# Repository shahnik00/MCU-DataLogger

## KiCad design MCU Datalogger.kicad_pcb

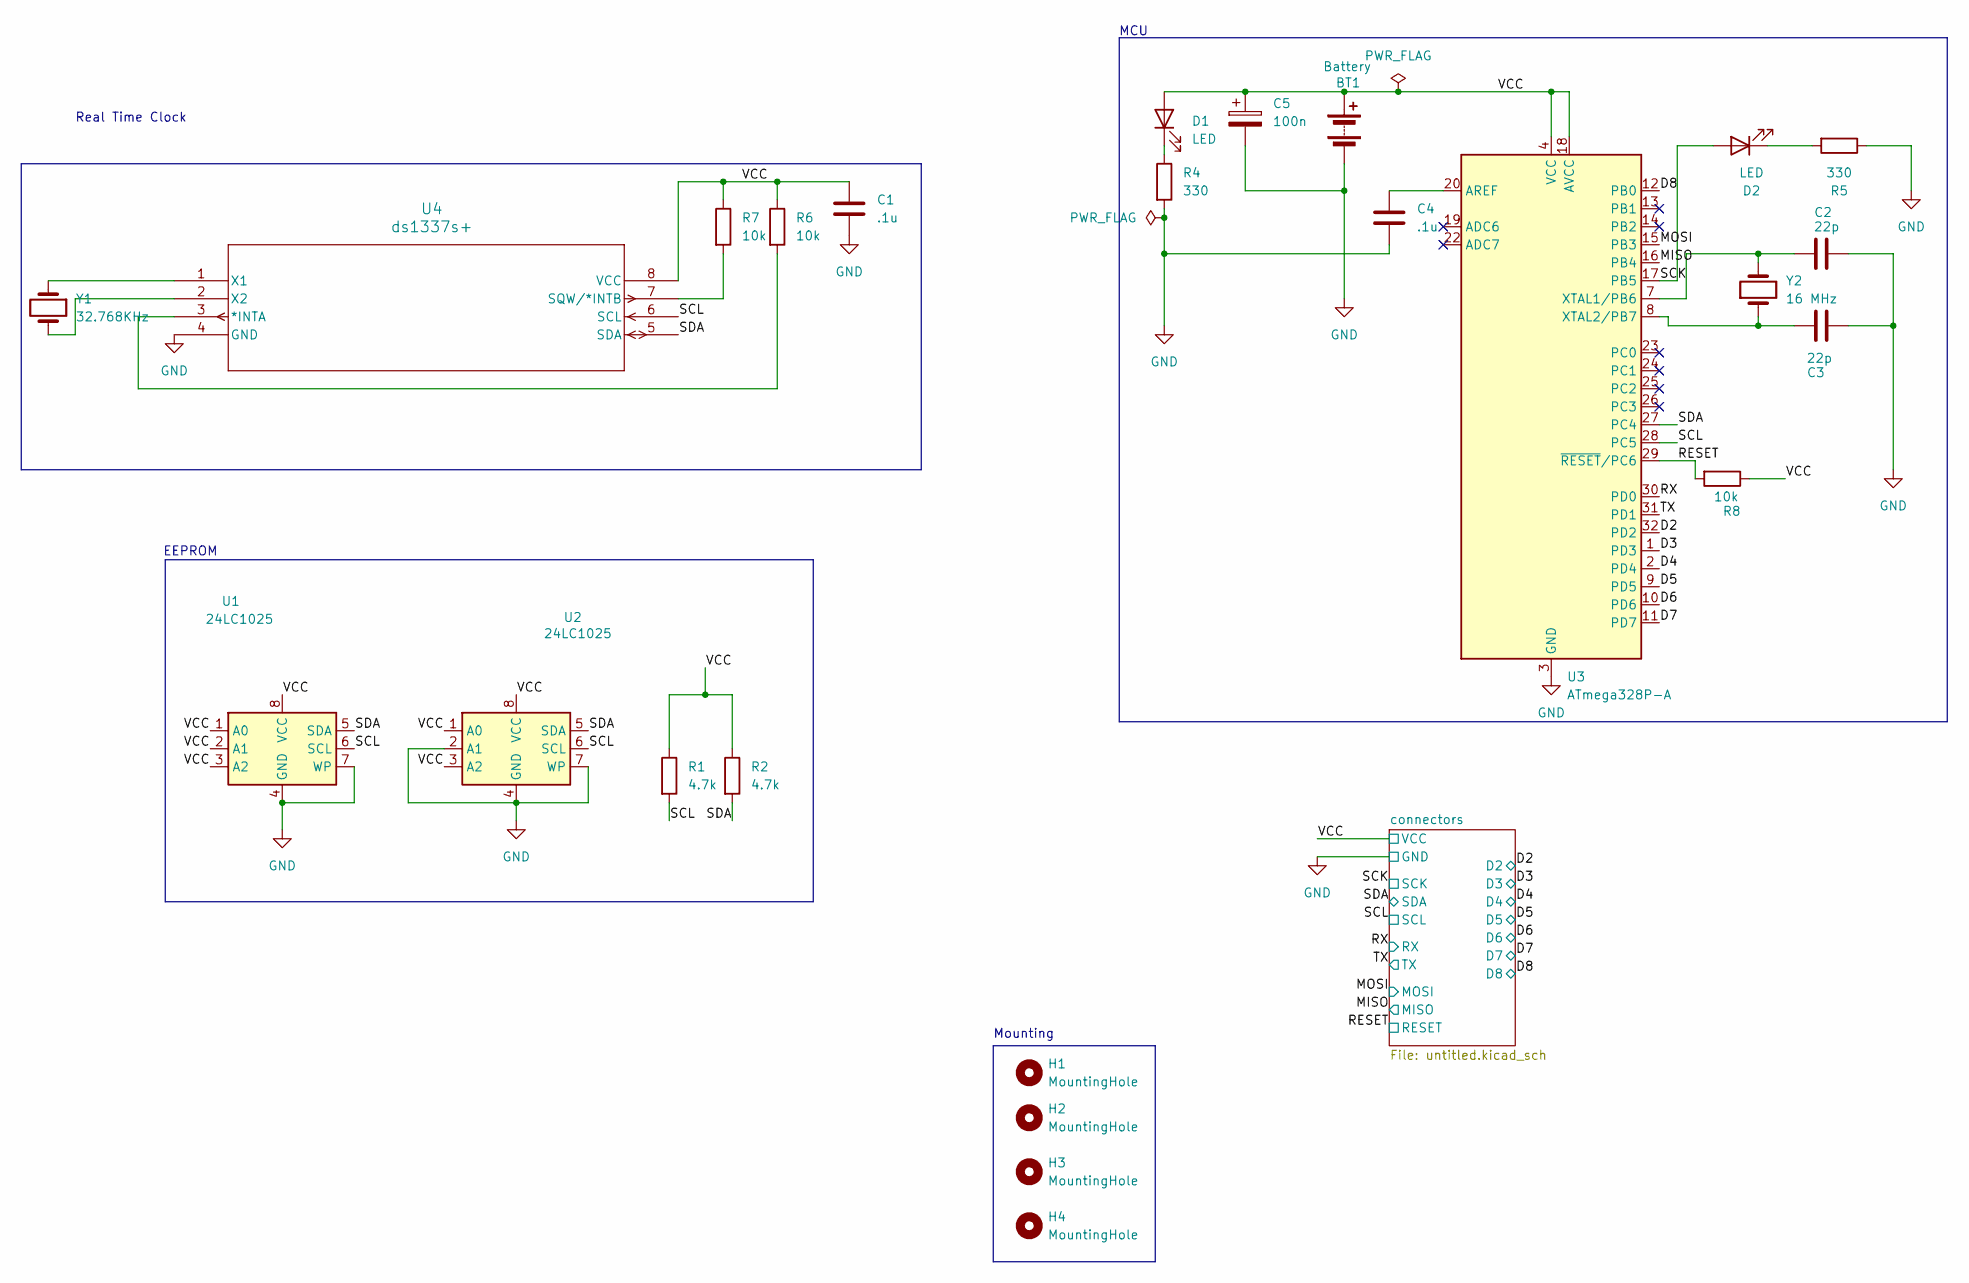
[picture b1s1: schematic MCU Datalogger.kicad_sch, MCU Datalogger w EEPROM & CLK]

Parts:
BT1: Battery; PinHeader_1x02_P2.54mm_Vertical
C1, C4: .1u; C_0805_2012Metric
C2, C3: 22p; C_0805_2012Metric
C5: 100n; C_0805_2012Metric
D1, D2: LED; LED_0805_2012Metric
H1, H2, H3, H4: MountingHole; MountingHole_2.1mm
R1, R2: 4.7k; R_0805_2012Metric
R4, R5: 330; R_0805_2012Metric
R6, R7, R8: 10k; R_0805_2012Metric
U1, U2: 24LC1025; SOIC-8_3.9x4.9mm_P1.27mm
U3: ATmega328P-A; TQFP-32_7x7mm_P0.8mm
U4: ds1337s+; 21-0041B_8_MXM
Y1: 32.768KHz; Crystal_SMD_5032-2Pin_5.0x3.2mm_HandSoldering
Y2: 16 MHz; Crystal_SMD_5032-2Pin_5.0x3.2mm_HandSoldering

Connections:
/D2: U3.32 (PD2); also elsewhere on the board
/D3: U3.1 (PD3); also elsewhere on the board
/D4: U3.2 (PD4); also elsewhere on the board
/D5: U3.9 (PD5); also elsewhere on the board
/D6: U3.10 (PD6); also elsewhere on the board
/D7: U3.11 (PD7); also elsewhere on the board
/D8: U3.12 (PB0); also elsewhere on the board
/MISO: U3.16 (PB4); also elsewhere on the board
/MOSI: U3.15 (PB3); also elsewhere on the board
/RESET: R8.2, U3.29 (~RESET/PC6); also elsewhere on the board
/RX: U3.30 (PD0); also elsewhere on the board
/SCK: D2.2 (A), U3.17 (PB5); also elsewhere on the board
/SCL: R1.2, U1.6 (SCL), U2.6 (SCL), U3.28 (PC5), U4.6 (SCL); also elsewhere on the board
/SDA: R2.2, U1.5 (SDA), U2.5 (SDA), U3.27 (PC4), U4.5 (SDA); also elsewhere on the board
/TX: U3.31 (PD1); also elsewhere on the board
/VCC: BT1.1 (+), C1.1, C5.1, D1.2 (A), R1.1, R2.1, R6.1, R7.1, R8.1, U1.1 (A0), U1.2 (A1), U1.3 (A2), U1.8 (VCC), U2.1 (A0), U2.3 (A2), U2.8 (VCC), U3.4 (VCC), U3.6 (VCC), U3.18 (AVCC), U4.8 (VCC); also elsewhere on the board
GND: BT1.2 (-), C1.2, C2.2, C3.2, C4.2, C5.2, R4.2, R5.1, U1.4 (GND), U1.7 (WP), U2.2 (A1), U2.4 (GND), U2.7 (WP), U3.3 (GND), U3.5 (GND), U3.21 (GND), U4.4 (GND); also elsewhere on the board
unnamed: D1.1 (K), R4.1
unnamed: D2.1 (K), R5.2
unnamed: C4.1, U3.20 (AREF)
unnamed: C2.1, U3.7 (XTAL1/PB6), Y2.2
unnamed: C3.1, U3.8 (XTAL2/PB7), Y2.1
unnamed: R6.2, U4.3 (*INTA)
unnamed: R7.2, U4.7 (SQW/*INTB)
unnamed: U4.1 (X1), Y1.1
unnamed: U4.2 (X2), Y1.2

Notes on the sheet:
MCU
Mounting
EEPROM
Real Time Clock

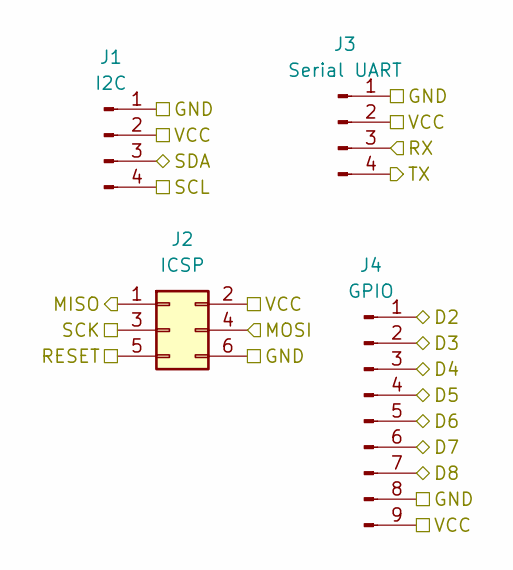
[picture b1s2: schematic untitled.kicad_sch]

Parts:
J1: I2C; PinHeader_1x04_P2.54mm_Vertical
J2: ICSP; PinHeader_2x03_P2.54mm_Vertical
J3: Serial UART; PinHeader_1x04_P2.54mm_Vertical
J4: GPIO; PinHeader_1x09_P2.54mm_Vertical

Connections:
/D2: J4.1; also elsewhere on the board
/D3: J4.2; also elsewhere on the board
/D4: J4.3; also elsewhere on the board
/D5: J4.4; also elsewhere on the board
/D6: J4.5; also elsewhere on the board
/D7: J4.6; also elsewhere on the board
/D8: J4.7; also elsewhere on the board
/MISO: J2.1; also elsewhere on the board
/MOSI: J2.4; also elsewhere on the board
/RESET: J2.5; also elsewhere on the board
/RX: J3.3; also elsewhere on the board
/SCK: J2.3; also elsewhere on the board
/SCL: J1.4; also elsewhere on the board
/SDA: J1.3; also elsewhere on the board
/TX: J3.4; also elsewhere on the board
/VCC: J1.2, J2.2, J3.2, J4.9; also elsewhere on the board
GND: J1.1, J2.6, J3.1, J4.8; also elsewhere on the board

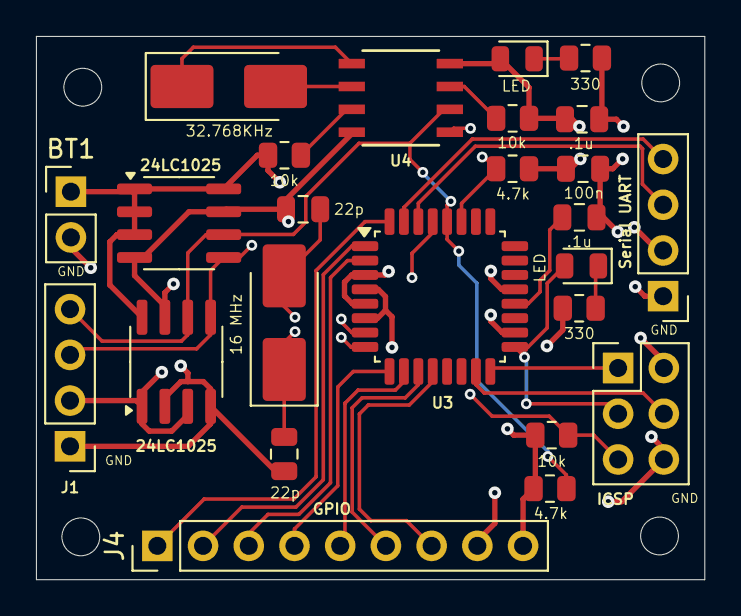
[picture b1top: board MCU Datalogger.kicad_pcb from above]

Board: 4 copper layers, 37.1 x 30.2 mm, 29 parts (0 on the bottom side), 26 nets.
